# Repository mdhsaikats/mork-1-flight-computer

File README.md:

# MORK-1 Flight Computer

A compact, real-time flight computer for model rockets, built on the ESP32-C3 Super Mini. It features attitude stabilization using a PID controller, altitude measurement, and status indication via LEDs.

---

## 🚀 Features

- **Attitude stabilization** using MPU6050 gyro/accelerometer and PID control
- **Altitude measurement** with BMP180 barometric sensor
- **Servo control** for pitch and yaw correction
- **Status LEDs** for system health and alerts
- **Serial debug output** for real-time monitoring

---

## 🛠️ Hardware Components

- **ESP32-C3 Super Mini**
- **MPU6050** (Gyro/Accelerometer, I2C)
- **BMP180** (Barometric Pressure Sensor, I2C)
- **2x Servos** (Pitch & Yaw control)
- **Red LED** (Alert)
- **Green LED** (System OK)
- **Resistors:** 220Ω for each LED

---

## 📐 Pin Connections

| Component         | ESP32-C3 Pin | Notes                        |
|-------------------|--------------|------------------------------|
| MPU6050 VCC       | 3V3          | Power                        |
| MPU6050 GND       | GND          | Ground                       |
| MPU6050 SDA       | GPIO 5       | I2C Data                     |
| MPU6050 SCL       | GPIO 6       | I2C Clock                    |
| BMP180 VCC        | 3V3          | Power                        |
| BMP180 GND        | GND          | Ground                       |
| BMP180 SDA        | GPIO 5       | I2C Data (shared)            |
| BMP180 SCL        | GPIO 6       | I2C Clock (shared)           |
| Servo Pitch       | GPIO 7       | PWM output                   |
| Servo Yaw         | GPIO 10      | PWM output                   |
| Red LED Anode     | GPIO 2       | 220Ω resistor in series      |
| Red LED Cathode   | GND          | Ground                       |
| Green LED Anode   | GPIO 3       | 220Ω resistor in series      |
| Green LED Cathode | GND          | Ground                       |

---

## 🖼️ Wiring Diagram (Text-Based)

```
ESP32-C3
  3V3 --------+------ MPU6050 VCC
              |------ BMP180 VCC
  GND -------+------ MPU6050 GND
             |------ BMP180 GND
             |------ LEDs Cathode (via resistor)
 GPIO5 SDA --+------ MPU6050 SDA
             |------ BMP180 SDA
 GPIO6 SCL --+------ MPU6050 SCL
             |------ BMP180 SCL
 GPIO7 ------> Servo Pitch (PWM)
 GPIO10 -----> Servo Yaw (PWM)
 GPIO2 ------> Red LED Anode (via 220Ω)
 GPIO3 ------> Green LED Anode (via 220Ω)
```

---

## ⚡ Wiring Notes

- **I2C Bus:** Both sensors share SDA (GPIO 5) and SCL (GPIO 6).
- **LEDs:** Use 220Ω resistors in series with each LED anode.
- **Servos:** Connect signal wires to GPIO 7 (Pitch) and GPIO 10 (Yaw). Power from 3.3V or external supply if needed.
- **Ground:** Ensure all components share a common GND.

---

## 📦 Project Structure

- `flightcomputer.c++` – Main project source file

---

## 🚦 System Behavior

- **Green LED ON:** System initialized and sensors OK
- **Red LED ON:** Sensor error or excessive rotation detected
- **Servos:** Actively stabilize rocket using PID
- **Serial Output:** Real-time debug info (gyro, servo, altitude)

---

## 🚀 Getting Started

1. **Wire components** as per the diagram above.
2. **Flash `flightcomputer.c++`** to your ESP32-C3 Super Mini.
3. **Open Serial Monitor** at 115200 baud for debug output.
4. **Power up** and observe stabilization and sensor readings.

---

## 📝 License

MIT License. See [LICENSE](LICENSE) for details.

---

## 🙌 Credits

Project by [Your Name].

---

> **Tip:** For a graphical wiring diagram, use [Fritzing](https://fritzing.org/) or similar tools.

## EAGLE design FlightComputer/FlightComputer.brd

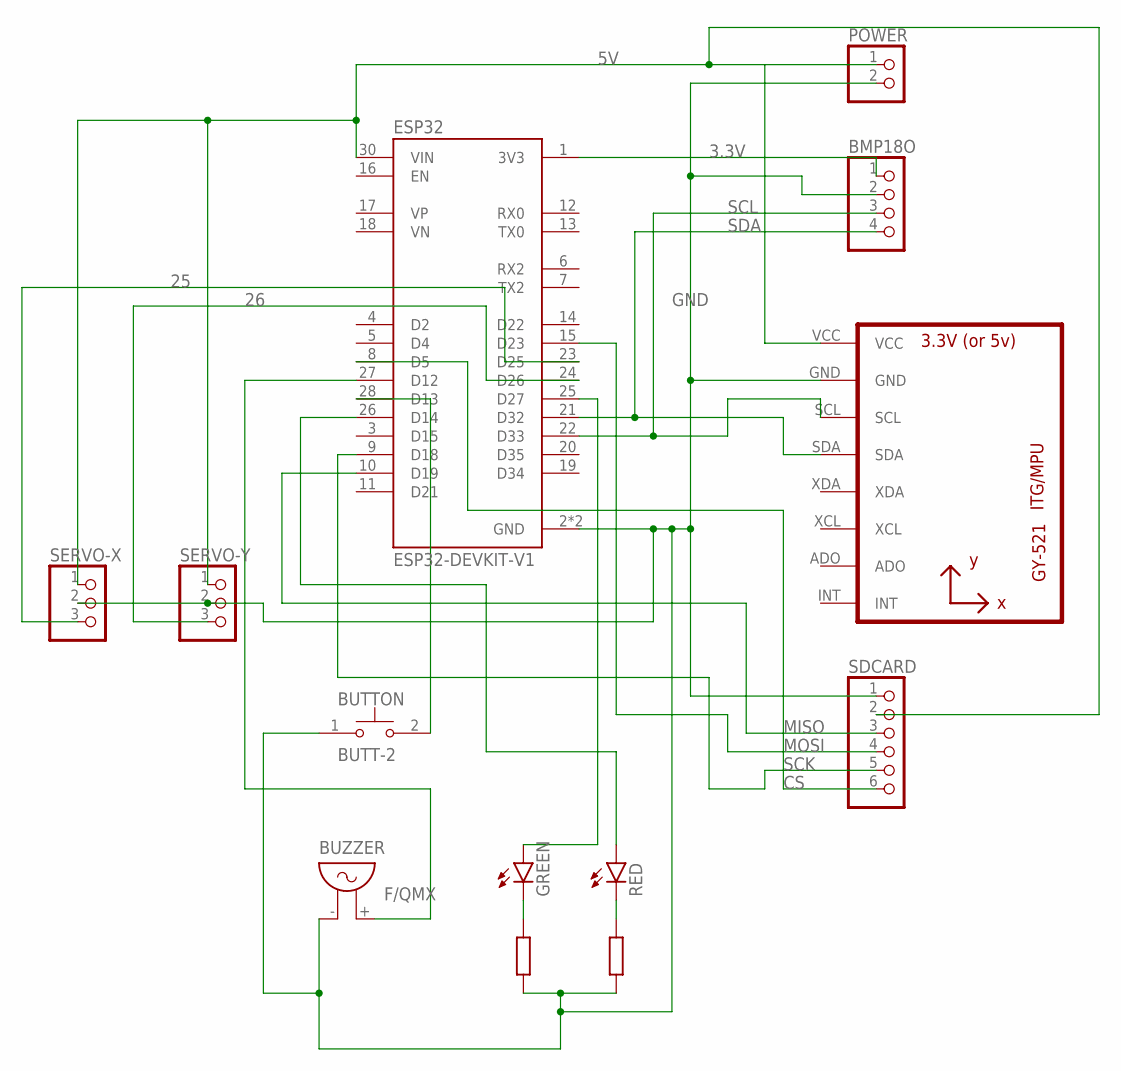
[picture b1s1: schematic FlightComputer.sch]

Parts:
BMP18O: PINHD-1X4; 1X04
BUTTON: BUTT-2; SW_BUTT-2
BUZZER: F/QMX
ESP32: ESP32-DEVKIT-V1; MODULE_ESP32_DEVKIT_V1
GREEN: LED3MM
POWER: PINHD-1X2; 1X02
RED: LED3MM
SDCARD: PINHD-1X6; 1X06
SERVO-X: PINHD-1X3; 1X03
SERVO-Y: PINHD-1X3; 1X03
U2: GY-521MPU6050; GY-521

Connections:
3.3V: BMP18O.1, ESP32.1 (3V3)
5V: ESP32.30 (VIN), POWER.1, SDCARD.2, SERVO-X.1, SERVO-Y.1, U2.VCC
25: ESP32.23 (D25), SERVO-X.3
26: ESP32.24 (D26), SERVO-Y.3
CS: ESP32.8 (D5), SDCARD.6
GND: BMP18O.2, BUTTON.1, BUZZER.- (1), ESP32.2 (GND), ESP32.29 (GND), POWER.2, SDCARD.1, SERVO-X.2, SERVO-Y.2, U2.GND
MISO: ESP32.10 (D19), SDCARD.3
MOSI: ESP32.15 (D23), SDCARD.4
unnamed: ESP32.26 (D14), RED.A
unnamed: BUZZER.+ (2), ESP32.27 (D12)
unnamed: BUTTON.2, ESP32.28 (D13)
unnamed: ESP32.25 (D27), GREEN.A
SCK: ESP32.9 (D18), SDCARD.5
SCL: BMP18O.3, ESP32.22 (D33), U2.SCL
SDA: BMP18O.4, ESP32.21 (D32), U2.SDA

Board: 2 copper layers, 11 parts (0 on the bottom side), 15 nets, no tracks yet.

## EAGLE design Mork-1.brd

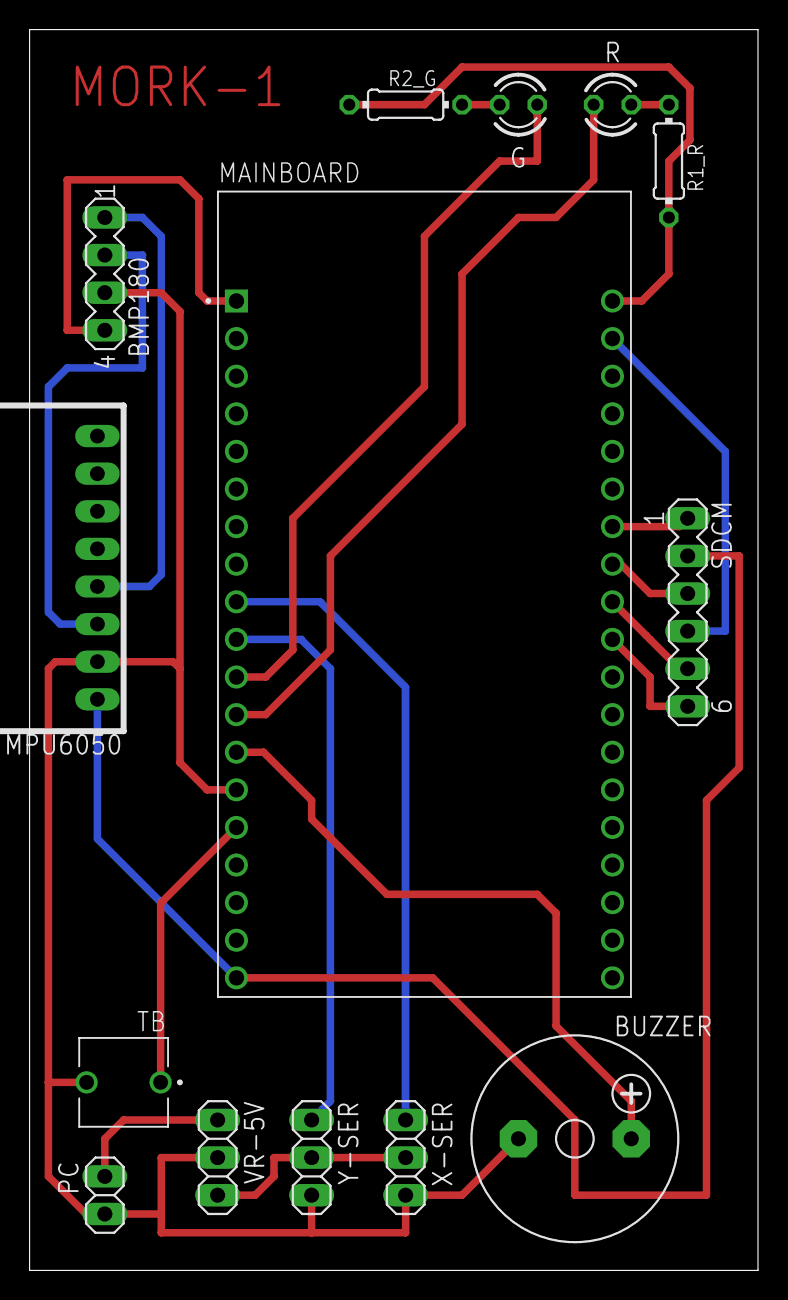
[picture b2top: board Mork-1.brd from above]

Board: 2 copper layers, 49.2 x 83.8 mm, 14 parts (0 on the bottom side), 21 nets.

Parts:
BMP180: MA04-1
BUZZER: F/CM12P
G: LED3MM
MAINBOARD: ESP32-DEVKITC-32D; MODULE_ESP32-DEVKITC-32D
MPU6050: GY-521PTH; GY-521
PC: 1X02
R: LED3MM
R1_R, R2_G: 0204/7
SDCM: MA06-1
TB: BUTT-2; SW_BUTT-2
VR-5V: 1X03
X-SER: 1X03
Y-SER: 1X03

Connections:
3.3V: BMP180.4, MAINBOARD.J2-1
5V: VR-5V.3, X-SER.2, Y-SER.2
5V-ESP: MAINBOARD.J2-19, MPU6050.VCC, SDCM.2
7.4V: PC.2, VR-5V.1
D12: BUZZER.+, MAINBOARD.J2-13
D13: MAINBOARD.J2-15, TB.1
D14: MAINBOARD.J2-12, R.A
D25: MAINBOARD.J2-9, X-SER.1
D26: MAINBOARD.J2-10, Y-SER.1
D27: G.A, MAINBOARD.J2-11
GND: BMP180.3, BUZZER.-, MAINBOARD.J2-14, MPU6050.GND, PC.1, TB.2, VR-5V.2, X-SER.3, Y-SER.3
GND2: MAINBOARD.J3-7, SDCM.1
GND3: MAINBOARD.J3-1, R1_R.1, R2_G.1
MISO: MAINBOARD.J3-8, SDCM.3
unnamed: MAINBOARD.J3-2, SDCM.4
unnamed: MAINBOARD.J3-10, SDCM.6
R1: R.K, R1_R.2
R2: G.K, R2_G.2
SCK: MAINBOARD.J3-9, SDCM.5
SCL: BMP180.2, MPU6050.SCL
SDA: BMP180.1, MPU6050.SDA

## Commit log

2025-10-02 init
2025-10-02 make it more robust
2025-10-02 make it more optimized
2025-10-03 added cam and pcb design
2025-10-11 add a new pcb design
2025-10-19 update the code
2025-11-24 change the code
2025-11-26 new code
